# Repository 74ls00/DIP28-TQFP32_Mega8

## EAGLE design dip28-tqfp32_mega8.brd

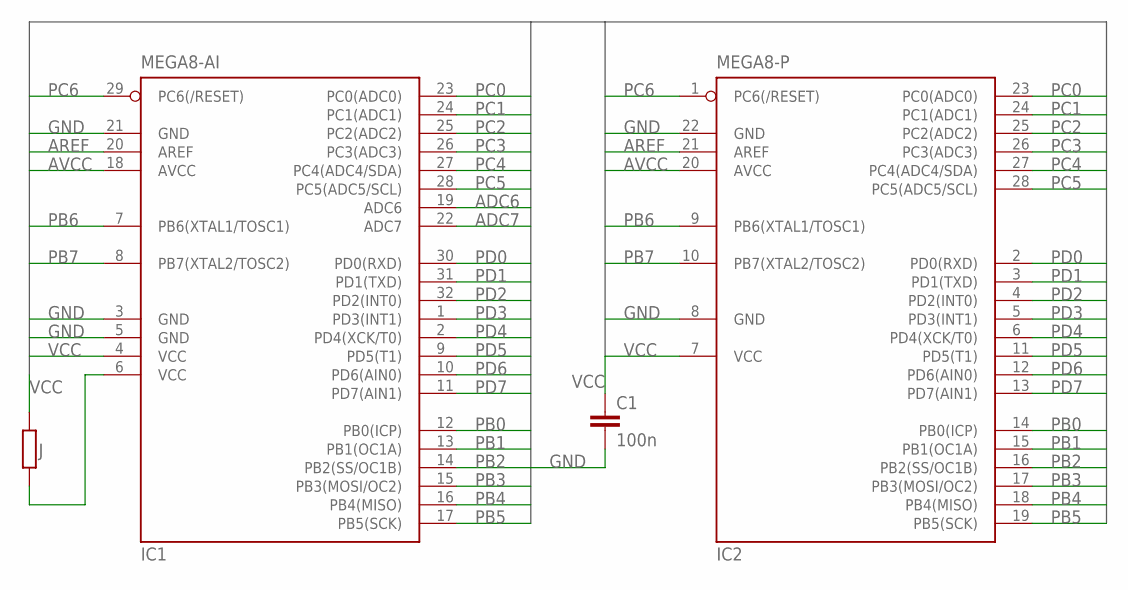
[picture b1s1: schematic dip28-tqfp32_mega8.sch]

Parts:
C1: 100n; C0805
IC1: MEGA8-AI; TQFP32-08
IC2: MEGA8-P; DIL28-3
J: R-EU_R1206W; R1206W

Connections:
ADC6: IC1.19 (ADC6)
ADC7: IC1.22 (ADC7)
AREF: IC1.20 (AREF), IC2.21 (AREF)
AVCC: IC1.18 (AVCC), IC2.20 (AVCC)
GND: C1.2, IC1.3 (GND), IC1.5 (GND), IC1.21 (GND), IC2.8 (GND), IC2.22 (GND)
unnamed: IC1.6 (VCC), J.1
PB0: IC1.12 (PB0(ICP)), IC2.14 (PB0(ICP))
PB1: IC1.13 (PB1(OC1A)), IC2.15 (PB1(OC1A))
PB2: IC1.14 (PB2(SS/OC1B)), IC2.16 (PB2(SS/OC1B))
PB3: IC1.15 (PB3(MOSI/OC2)), IC2.17 (PB3(MOSI/OC2))
PB4: IC1.16 (PB4(MISO)), IC2.18 (PB4(MISO))
PB5: IC1.17 (PB5(SCK)), IC2.19 (PB5(SCK))
PB6: IC1.7 (PB6(XTAL1/TOSC1)), IC2.9 (PB6(XTAL1/TOSC1))
PB7: IC1.8 (PB7(XTAL2/TOSC2)), IC2.10 (PB7(XTAL2/TOSC2))
PC0: IC1.23 (PC0(ADC0)), IC2.23 (PC0(ADC0))
PC1: IC1.24 (PC1(ADC1)), IC2.24 (PC1(ADC1))
PC2: IC1.25 (PC2(ADC2)), IC2.25 (PC2(ADC2))
PC3: IC1.26 (PC3(ADC3)), IC2.26 (PC3(ADC3))
PC4: IC1.27 (PC4(ADC4/SDA)), IC2.27 (PC4(ADC4/SDA))
PC5: IC1.28 (PC5(ADC5/SCL)), IC2.28 (PC5(ADC5/SCL))
PC6: IC1.29 (PC6(/RESET)), IC2.1 (PC6(/RESET))
PD0: IC1.30 (PD0(RXD)), IC2.2 (PD0(RXD))
PD1: IC1.31 (PD1(TXD)), IC2.3 (PD1(TXD))
PD2: IC1.32 (PD2(INT0)), IC2.4 (PD2(INT0))
PD3: IC1.1 (PD3(INT1)), IC2.5 (PD3(INT1))
PD4: IC1.2 (PD4(XCK/T0)), IC2.6 (PD4(XCK/T0))
PD5: IC1.9 (PD5(T1)), IC2.11 (PD5(T1))
PD6: IC1.10 (PD6(AIN0)), IC2.12 (PD6(AIN0))
PD7: IC1.11 (PD7(AIN1)), IC2.13 (PD7(AIN1))
VCC: C1.1, IC1.4 (VCC), IC2.7 (VCC), J.2

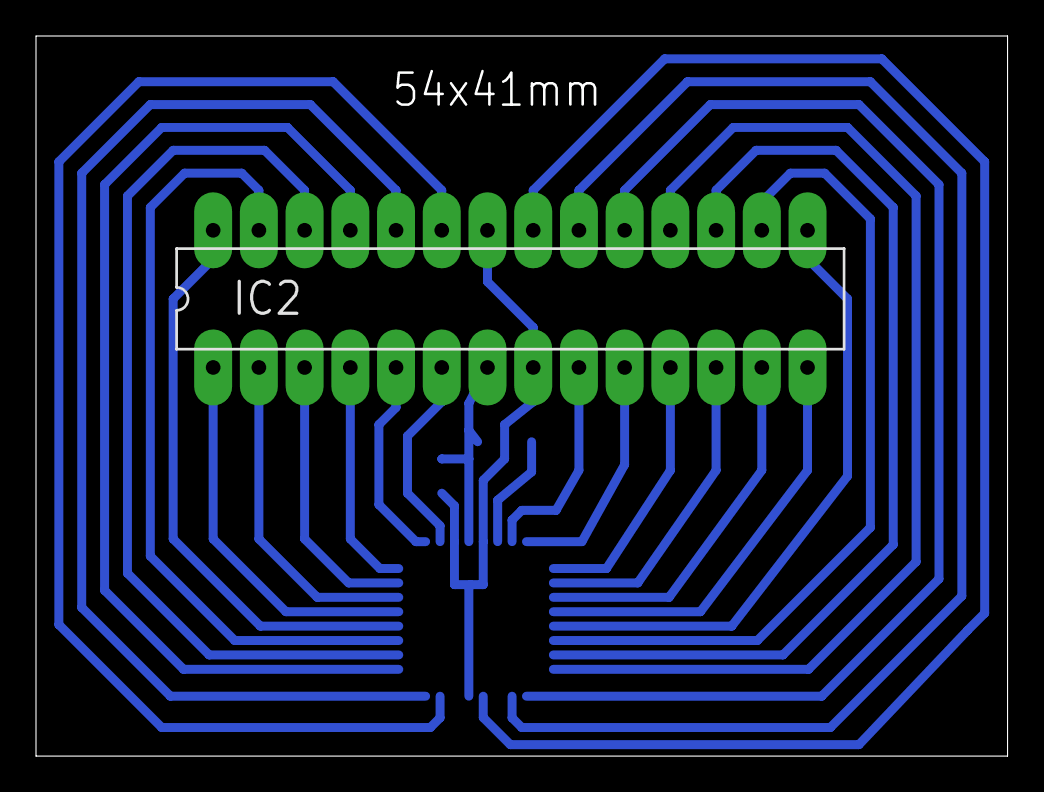
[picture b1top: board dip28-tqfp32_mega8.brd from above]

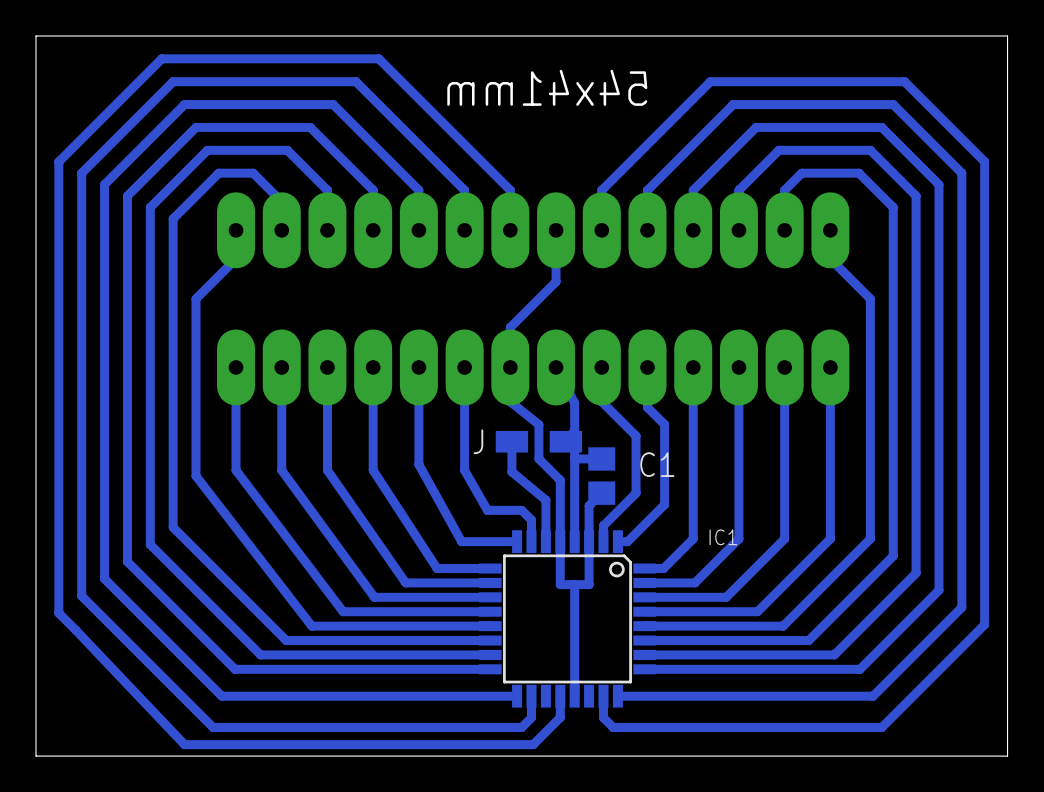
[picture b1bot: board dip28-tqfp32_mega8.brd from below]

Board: 2 copper layers, 54.0 x 40.0 mm, 4 parts (3 on the bottom side), 28 nets.
